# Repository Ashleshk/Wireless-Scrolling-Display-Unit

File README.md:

# Wireless-Scrolling-Display-Unit
 This project was buit for Academic Evaluation of term work for the Third year Mini Project  building in the subject of Electronic Sensor & Mini-Project in Course of E&TC 

## Working Project

## Won Project Exhibition Competition

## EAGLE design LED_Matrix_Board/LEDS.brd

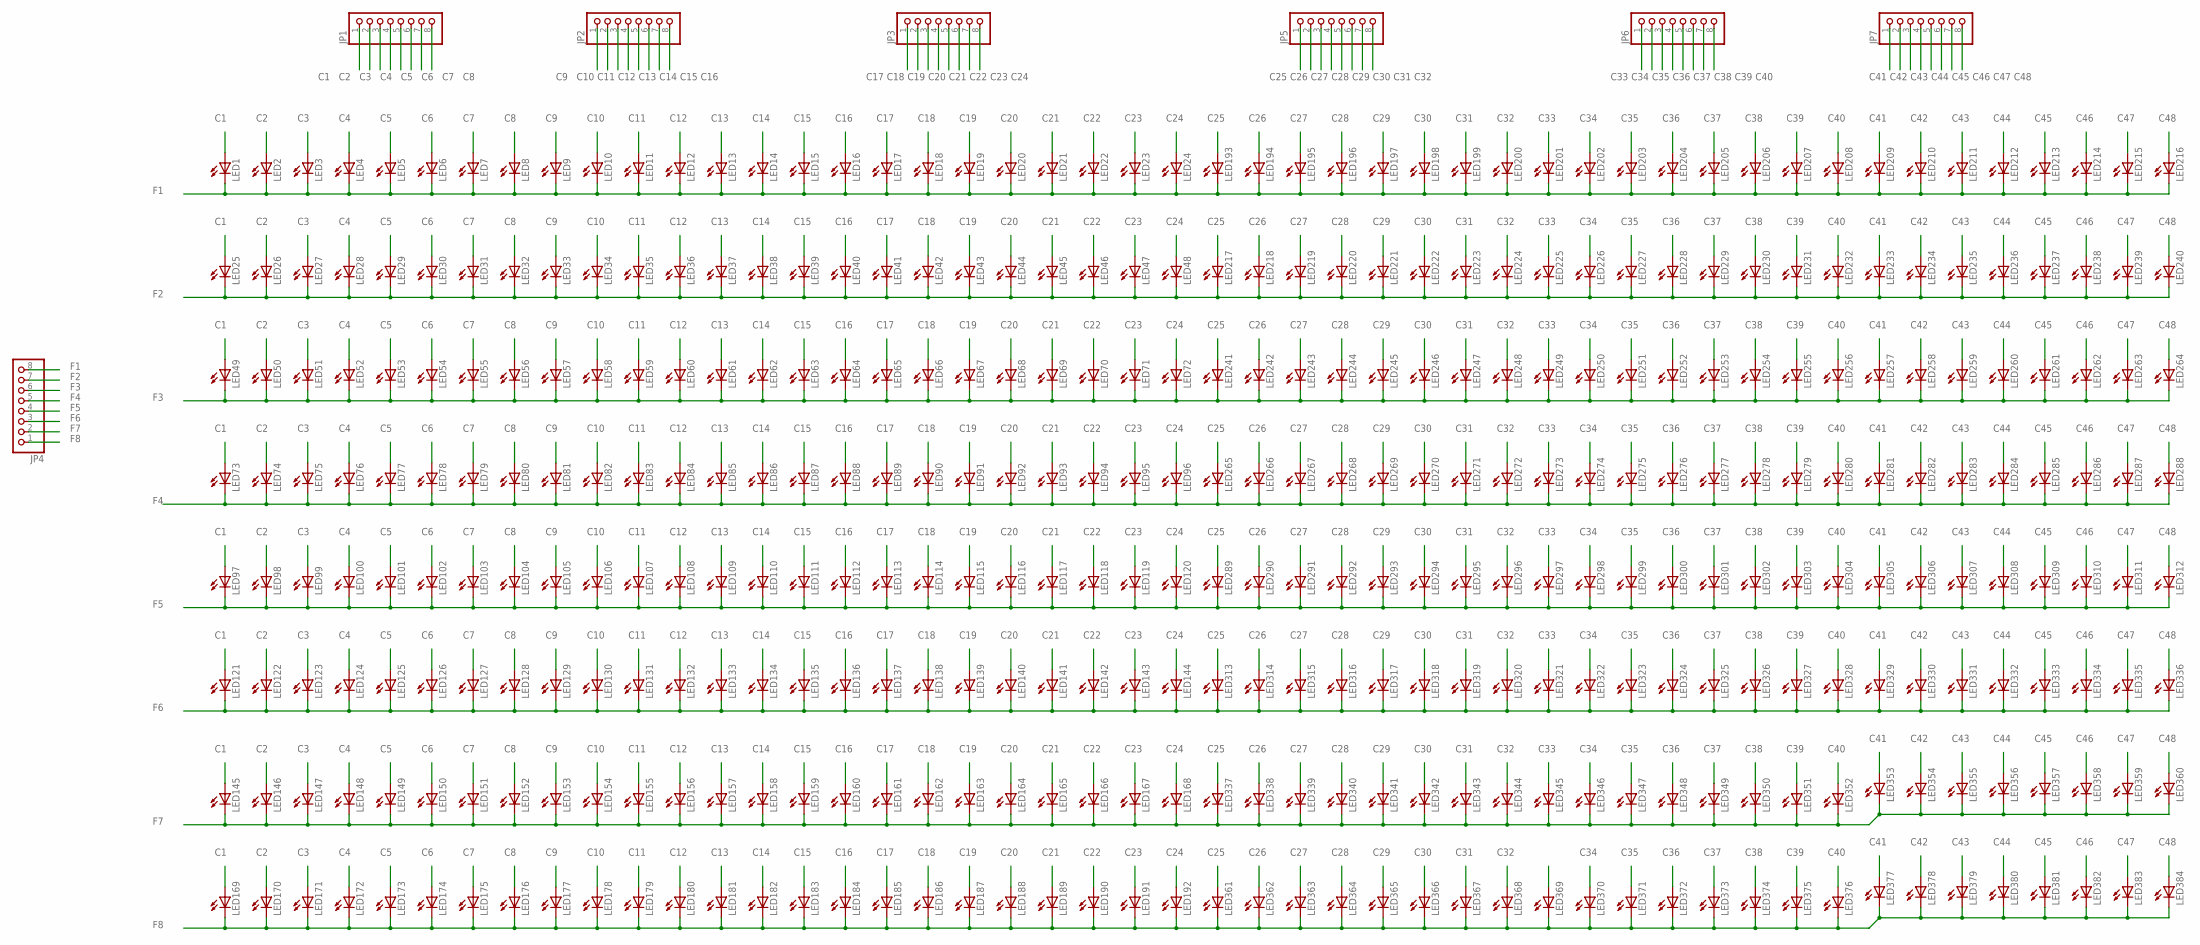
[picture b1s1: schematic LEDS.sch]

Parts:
JP1, JP2, JP3, JP4, JP5, JP6, JP7: PINHD-1X8; 1X08
LED1, LED2, LED3, LED4, LED5, LED6, LED7, LED8, LED9, LED10, LED11, LED12, LED13, LED14, LED15, LED16, LED17, LED18, LED19, LED20, LED21, LED22, LED23, LED24, LED25, LED26, LED27, LED28, LED29, LED30, LED31, LED32, LED33, LED34, LED35, LED36, LED37, LED38, LED39, LED40, LED41, LED42, LED43, LED44, LED45, LED46, LED47, LED48, LED49, LED50, LED51, LED52, LED53, LED54, LED55, LED56, LED57, LED58, LED59, LED60, LED61, LED62, LED63, LED64, LED65, LED66, LED67, LED68, LED69, LED70, LED71, LED72, LED73, LED74, LED75, LED76, LED77, LED78, LED79, LED80, LED81, LED82, LED83, LED84, LED85, LED86, LED87, LED88, LED89, LED90, LED91, LED92, LED93, LED94, LED95, LED96, LED97, LED98, LED99, LED100, LED101, LED102, LED103, LED104, LED105, LED106, LED107, LED108, LED109, LED110, LED111, LED112, LED113, LED114, LED115, LED116, LED117, LED118, LED119, LED120, LED121, LED122, LED123, LED124, LED125, LED126, LED127, LED128, LED129, LED130, LED131, LED132, LED133, LED134, LED135, LED136, LED137, LED138, LED139, LED140, LED141, LED142, LED143, LED144, LED145, LED146, LED147, LED148, LED149, LED150, LED151, LED152, LED153, LED154, LED155, LED156, LED157, LED158, LED159, LED160, LED161, LED162, LED163, LED164, LED165, LED166, LED167, LED168, LED169, LED170, LED171, LED172, LED173, LED174, LED175, LED176, LED177, LED178, LED179, LED180, LED181, LED182, LED183, LED184, LED185, LED186, LED187, LED188, LED189, LED190, LED191, LED192, LED193, LED194, LED195, LED196, LED197, LED198, LED199, LED200, LED201, LED202, LED203, LED204, LED205, LED206, LED207, LED208, LED209, LED210, LED211, LED212, LED213, LED214, LED215, LED216, LED217, LED218, LED219, LED220, LED221, LED222, LED223, LED224, LED225, LED226, LED227, LED228, LED229, LED230, LED231, LED232, LED233, LED234, LED235, LED236, LED237, LED238, LED239, LED240, LED241, LED242, LED243, LED244, LED245, LED246, LED247, LED248, LED249, LED250, LED251, LED252, LED253, LED254, LED255, LED256, LED257, LED258, LED259, LED260, LED261, LED262, LED263, LED264, LED265, LED266, LED267, LED268, LED269, LED270, LED271, LED272, LED273, LED274, LED275, LED276, LED277, LED278, LED279, LED280, LED281, LED282, LED283, LED284, LED285, LED286, LED287, LED288, LED289, LED290, LED291, LED292, LED293, LED294, LED295, LED296, LED297, LED298, LED299, LED300, LED301, LED302, LED303, LED304, LED305, LED306, LED307, LED308, LED309, LED310, LED311, LED312, LED313, LED314, LED315, LED316, LED317, LED318, LED319, LED320, LED321, LED322, LED323, LED324, LED325, LED326, LED327, LED328, LED329, LED330, LED331, LED332, LED333, LED334, LED335, LED336, LED337, LED338, LED339, LED340, LED341, LED342, LED343, LED344, LED345, LED346, LED347, LED348, LED349, LED350, LED351, LED352, LED353, LED354, LED355, LED356, LED357, LED358, LED359, LED360, LED361, LED362, LED363, LED364, LED365, LED366, LED367, LED368, LED369, LED370, LED371, LED372, LED373, LED374, LED375, LED376, LED377, LED378, LED379, LED380, LED381, LED382, LED383, LED384: LED5MM

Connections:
C1: JP1.1, LED1.A, LED25.A, LED49.A, LED73.A, LED97.A, LED121.A, LED145.A, LED169.A
C2: JP1.2, LED2.A, LED26.A, LED50.A, LED74.A, LED98.A, LED122.A, LED146.A, LED170.A
C3: JP1.3, LED3.A, LED27.A, LED51.A, LED75.A, LED99.A, LED123.A, LED147.A, LED171.A
C4: JP1.4, LED4.A, LED28.A, LED52.A, LED76.A, LED100.A, LED124.A, LED148.A, LED172.A
C5: JP1.5, LED5.A, LED29.A, LED53.A, LED77.A, LED101.A, LED125.A, LED149.A, LED173.A
C6: JP1.6, LED6.A, LED30.A, LED54.A, LED78.A, LED102.A, LED126.A, LED150.A, LED174.A
C7: JP1.7, LED7.A, LED31.A, LED55.A, LED79.A, LED103.A, LED127.A, LED151.A, LED175.A
C8: JP1.8, LED8.A, LED32.A, LED56.A, LED80.A, LED104.A, LED128.A, LED152.A, LED176.A
C9: JP2.1, LED9.A, LED33.A, LED57.A, LED81.A, LED105.A, LED129.A, LED153.A, LED177.A
C10: JP2.2, LED10.A, LED34.A, LED58.A, LED82.A, LED106.A, LED130.A, LED154.A, LED178.A
C11: JP2.3, LED11.A, LED35.A, LED59.A, LED83.A, LED107.A, LED131.A, LED155.A, LED179.A
C12: JP2.4, LED12.A, LED36.A, LED60.A, LED84.A, LED108.A, LED132.A, LED156.A, LED180.A
C13: JP2.5, LED13.A, LED37.A, LED61.A, LED85.A, LED109.A, LED133.A, LED157.A, LED181.A
C14: JP2.6, LED14.A, LED38.A, LED62.A, LED86.A, LED110.A, LED134.A, LED158.A, LED182.A
C15: JP2.7, LED15.A, LED39.A, LED63.A, LED87.A, LED111.A, LED135.A, LED159.A, LED183.A
C16: JP2.8, LED16.A, LED40.A, LED64.A, LED88.A, LED112.A, LED136.A, LED160.A, LED184.A
C17: JP3.1, LED17.A, LED41.A, LED65.A, LED89.A, LED113.A, LED137.A, LED161.A, LED185.A
C18: JP3.2, LED18.A, LED42.A, LED66.A, LED90.A, LED114.A, LED138.A, LED162.A, LED186.A
C19: JP3.3, LED19.A, LED43.A, LED67.A, LED91.A, LED115.A, LED139.A, LED163.A, LED187.A
C20: JP3.4, LED20.A, LED44.A, LED68.A, LED92.A, LED116.A, LED140.A, LED164.A, LED188.A
C21: JP3.5, LED21.A, LED45.A, LED69.A, LED93.A, LED117.A, LED141.A, LED165.A, LED189.A
C22: JP3.6, LED22.A, LED46.A, LED70.A, LED94.A, LED118.A, LED142.A, LED166.A, LED190.A
C23: JP3.7, LED23.A, LED47.A, LED71.A, LED95.A, LED119.A, LED143.A, LED167.A, LED191.A
C24: JP3.8, LED24.A, LED48.A, LED72.A, LED96.A, LED120.A, LED144.A, LED168.A, LED192.A
C25: JP5.1, LED193.A, LED217.A, LED241.A, LED265.A, LED289.A, LED313.A, LED337.A, LED361.A
C26: JP5.2, LED194.A, LED218.A, LED242.A, LED266.A, LED290.A, LED314.A, LED338.A, LED362.A
C27: JP5.3, LED195.A, LED219.A, LED243.A, LED267.A, LED291.A, LED315.A, LED339.A, LED363.A
C28: JP5.4, LED196.A, LED220.A, LED244.A, LED268.A, LED292.A, LED316.A, LED340.A, LED364.A
C29: JP5.5, LED197.A, LED221.A, LED245.A, LED269.A, LED293.A, LED317.A, LED341.A, LED365.A
C30: JP5.6, LED198.A, LED222.A, LED246.A, LED270.A, LED294.A, LED318.A, LED342.A, LED366.A
C31: JP5.7, LED199.A, LED223.A, LED247.A, LED271.A, LED295.A, LED319.A, LED343.A, LED367.A
C32: JP5.8, LED200.A, LED224.A, LED248.A, LED272.A, LED296.A, LED320.A, LED344.A, LED368.A
C33: JP6.1, LED201.A, LED225.A, LED249.A, LED273.A, LED297.A, LED321.A, LED345.A
C34: JP6.2, LED202.A, LED226.A, LED250.A, LED274.A, LED298.A, LED322.A, LED346.A, LED370.A
C35: JP6.3, LED203.A, LED227.A, LED251.A, LED275.A, LED299.A, LED323.A, LED347.A, LED371.A
C36: JP6.4, LED204.A, LED228.A, LED252.A, LED276.A, LED300.A, LED324.A, LED348.A, LED372.A
C37: JP6.5, LED205.A, LED229.A, LED253.A, LED277.A, LED301.A, LED325.A, LED349.A, LED373.A
C38: JP6.6, LED206.A, LED230.A, LED254.A, LED278.A, LED302.A, LED326.A, LED350.A, LED374.A
C39: JP6.7, LED207.A, LED231.A, LED255.A, LED279.A, LED303.A, LED327.A, LED351.A, LED375.A
C40: JP6.8, LED208.A, LED232.A, LED256.A, LED280.A, LED304.A, LED328.A, LED352.A, LED376.A
C41: JP7.1, LED209.A, LED233.A, LED257.A, LED281.A, LED305.A, LED329.A, LED353.A, LED369.A, LED377.A
C42: JP7.2, LED210.A, LED234.A, LED258.A, LED282.A, LED306.A, LED330.A, LED354.A, LED378.A
C43: JP7.3, LED211.A, LED235.A, LED259.A, LED283.A, LED307.A, LED331.A, LED355.A, LED379.A
C44: JP7.4, LED212.A, LED236.A, LED260.A, LED284.A, LED308.A, LED332.A, LED356.A, LED380.A
C45: JP7.5, LED213.A, LED237.A, LED261.A, LED285.A, LED309.A, LED333.A, LED357.A, LED381.A
C46: JP7.6, LED214.A, LED238.A, LED262.A, LED286.A, LED310.A, LED334.A, LED358.A, LED382.A
C47: JP7.7, LED215.A, LED239.A, LED263.A, LED287.A, LED311.A, LED335.A, LED359.A, LED383.A
C48: JP7.8, LED216.A, LED240.A, LED264.A, LED288.A, LED312.A, LED336.A, LED360.A, LED384.A
F1: JP4.8, LED1.K (C), LED2.K (C), LED3.K (C), LED4.K (C), LED5.K (C), LED6.K (C), LED7.K (C), LED8.K (C), LED9.K (C), LED10.K (C), LED11.K (C), LED12.K (C), LED13.K (C), LED14.K (C), LED15.K (C), LED16.K (C), LED17.K (C), LED18.K (C), LED19.K (C), LED20.K (C), LED21.K (C), LED22.K (C), LED23.K (C), LED24.K (C), LED193.K (C), LED194.K (C), LED195.K (C), LED196.K (C), LED197.K (C), LED198.K (C), LED199.K (C), LED200.K (C), LED201.K (C), LED202.K (C), LED203.K (C), LED204.K (C), LED205.K (C), LED206.K (C), LED207.K (C), LED208.K (C), LED209.K (C), LED210.K (C), LED211.K (C), LED212.K (C), LED213.K (C), LED214.K (C), LED215.K (C), LED216.K (C)
F2: JP4.7, LED25.K (C), LED26.K (C), LED27.K (C), LED28.K (C), LED29.K (C), LED30.K (C), LED31.K (C), LED32.K (C), LED33.K (C), LED34.K (C), LED35.K (C), LED36.K (C), LED37.K (C), LED38.K (C), LED39.K (C), LED40.K (C), LED41.K (C), LED42.K (C), LED43.K (C), LED44.K (C), LED45.K (C), LED46.K (C), LED47.K (C), LED48.K (C), LED217.K (C), LED218.K (C), LED219.K (C), LED220.K (C), LED221.K (C), LED222.K (C), LED223.K (C), LED224.K (C), LED225.K (C), LED226.K (C), LED227.K (C), LED228.K (C), LED229.K (C), LED230.K (C), LED231.K (C), LED232.K (C), LED233.K (C), LED234.K (C), LED235.K (C), LED236.K (C), LED237.K (C), LED238.K (C), LED239.K (C), LED240.K (C)
F3: JP4.6, LED49.K (C), LED50.K (C), LED51.K (C), LED52.K (C), LED53.K (C), LED54.K (C), LED55.K (C), LED56.K (C), LED57.K (C), LED58.K (C), LED59.K (C), LED60.K (C), LED61.K (C), LED62.K (C), LED63.K (C), LED64.K (C), LED65.K (C), LED66.K (C), LED67.K (C), LED68.K (C), LED69.K (C), LED70.K (C), LED71.K (C), LED72.K (C), LED241.K (C), LED242.K (C), LED243.K (C), LED244.K (C), LED245.K (C), LED246.K (C), LED247.K (C), LED248.K (C), LED249.K (C), LED250.K (C), LED251.K (C), LED252.K (C), LED253.K (C), LED254.K (C), LED255.K (C), LED256.K (C), LED257.K (C), LED258.K (C), LED259.K (C), LED260.K (C), LED261.K (C), LED262.K (C), LED263.K (C), LED264.K (C)
F4: JP4.5, LED73.K (C), LED74.K (C), LED75.K (C), LED76.K (C), LED77.K (C), LED78.K (C), LED79.K (C), LED80.K (C), LED81.K (C), LED82.K (C), LED83.K (C), LED84.K (C), LED85.K (C), LED86.K (C), LED87.K (C), LED88.K (C), LED89.K (C), LED90.K (C), LED91.K (C), LED92.K (C), LED93.K (C), LED94.K (C), LED95.K (C), LED96.K (C), LED265.K (C), LED266.K (C), LED267.K (C), LED268.K (C), LED269.K (C), LED270.K (C), LED271.K (C), LED272.K (C), LED273.K (C), LED274.K (C), LED275.K (C), LED276.K (C), LED277.K (C), LED278.K (C), LED279.K (C), LED280.K (C), LED281.K (C), LED282.K (C), LED283.K (C), LED284.K (C), LED285.K (C), LED286.K (C), LED287.K (C), LED288.K (C)
F5: JP4.4, LED97.K (C), LED98.K (C), LED99.K (C), LED100.K (C), LED101.K (C), LED102.K (C), LED103.K (C), LED104.K (C), LED105.K (C), LED106.K (C), LED107.K (C), LED108.K (C), LED109.K (C), LED110.K (C), LED111.K (C), LED112.K (C), LED113.K (C), LED114.K (C), LED115.K (C), LED116.K (C), LED117.K (C), LED118.K (C), LED119.K (C), LED120.K (C), LED289.K (C), LED290.K (C), LED291.K (C), LED292.K (C), LED293.K (C), LED294.K (C), LED295.K (C), LED296.K (C), LED297.K (C), LED298.K (C), LED299.K (C), LED300.K (C), LED301.K (C), LED302.K (C), LED303.K (C), LED304.K (C), LED305.K (C), LED306.K (C), LED307.K (C), LED308.K (C), LED309.K (C), LED310.K (C), LED311.K (C), LED312.K (C)
F6: JP4.3, LED121.K (C), LED122.K (C), LED123.K (C), LED124.K (C), LED125.K (C), LED126.K (C), LED127.K (C), LED128.K (C), LED129.K (C), LED130.K (C), LED131.K (C), LED132.K (C), LED133.K (C), LED134.K (C), LED135.K (C), LED136.K (C), LED137.K (C), LED138.K (C), LED139.K (C), LED140.K (C), LED141.K (C), LED142.K (C), LED143.K (C), LED144.K (C), LED313.K (C), LED314.K (C), LED315.K (C), LED316.K (C), LED317.K (C), LED318.K (C), LED319.K (C), LED320.K (C), LED321.K (C), LED322.K (C), LED323.K (C), LED324.K (C), LED325.K (C), LED326.K (C), LED327.K (C), LED328.K (C), LED329.K (C), LED330.K (C), LED331.K (C), LED332.K (C), LED333.K (C), LED334.K (C), LED335.K (C), LED336.K (C)
F7: JP4.2, LED145.K (C), LED146.K (C), LED147.K (C), LED148.K (C), LED149.K (C), LED150.K (C), LED151.K (C), LED152.K (C), LED153.K (C), LED154.K (C), LED155.K (C), LED156.K (C), LED157.K (C), LED158.K (C), LED159.K (C), LED160.K (C), LED161.K (C), LED162.K (C), LED163.K (C), LED164.K (C), LED165.K (C), LED166.K (C), LED167.K (C), LED168.K (C), LED337.K (C), LED338.K (C), LED339.K (C), LED340.K (C), LED341.K (C), LED342.K (C), LED343.K (C), LED344.K (C), LED345.K (C), LED346.K (C), LED347.K (C), LED348.K (C), LED349.K (C), LED350.K (C), LED351.K (C), LED352.K (C), LED353.K (C), LED354.K (C), LED355.K (C), LED356.K (C), LED357.K (C), LED358.K (C), LED359.K (C), LED360.K (C)
F8: JP4.1, LED169.K (C), LED170.K (C), LED171.K (C), LED172.K (C), LED173.K (C), LED174.K (C), LED175.K (C), LED176.K (C), LED177.K (C), LED178.K (C), LED179.K (C), LED180.K (C), LED181.K (C), LED182.K (C), LED183.K (C), LED184.K (C), LED185.K (C), LED186.K (C), LED187.K (C), LED188.K (C), LED189.K (C), LED190.K (C), LED191.K (C), LED192.K (C), LED361.K (C), LED362.K (C), LED363.K (C), LED364.K (C), LED365.K (C), LED366.K (C), LED367.K (C), LED368.K (C), LED369.K (C), LED370.K (C), LED371.K (C), LED372.K (C), LED373.K (C), LED374.K (C), LED375.K (C), LED376.K (C), LED377.K (C), LED378.K (C), LED379.K (C), LED380.K (C), LED381.K (C), LED382.K (C), LED383.K (C), LED384.K (C)

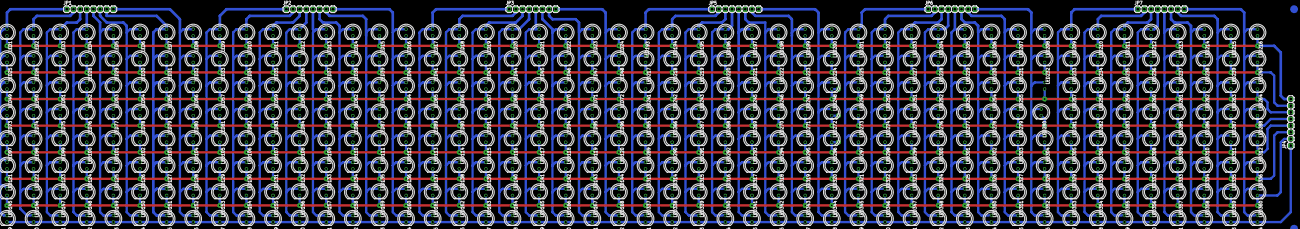
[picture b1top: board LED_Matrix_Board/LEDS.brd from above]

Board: 2 copper layers, 391 parts (1 on the bottom side), 56 nets.

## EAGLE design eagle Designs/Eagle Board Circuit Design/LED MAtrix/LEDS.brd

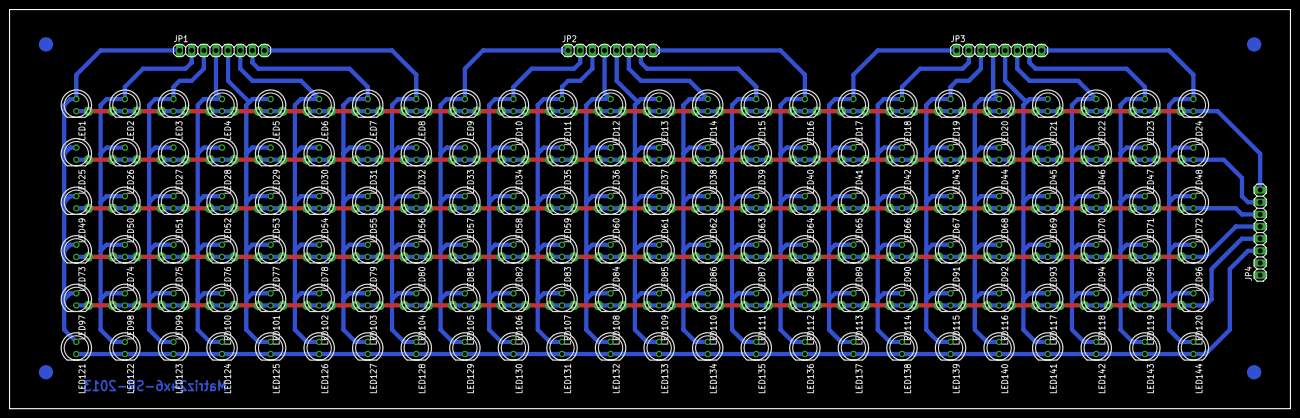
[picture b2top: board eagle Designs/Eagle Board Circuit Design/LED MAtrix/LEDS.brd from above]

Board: 2 copper layers, 267.9 x 83.5 mm, 148 parts (0 on the bottom side), 30 nets.

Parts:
JP1, JP2, JP3, JP4: 1X08
LED1, LED2, LED3, LED4, LED5, LED6, LED7, LED8, LED9, LED10, LED11, LED12, LED13, LED14, LED15, LED16, LED17, LED18, LED19, LED20, LED21, LED22, LED23, LED24, LED25, LED26, LED27, LED28, LED29, LED30, LED31, LED32, LED33, LED34, LED35, LED36, LED37, LED38, LED39, LED40, LED41, LED42, LED43, LED44, LED45, LED46, LED47, LED48, LED49, LED50, LED51, LED52, LED53, LED54, LED55, LED56, LED57, LED58, LED59, LED60, LED61, LED62, LED63, LED64, LED65, LED66, LED67, LED68, LED69, LED70, LED71, LED72, LED73, LED74, LED75, LED76, LED77, LED78, LED79, LED80, LED81, LED82, LED83, LED84, LED85, LED86, LED87, LED88, LED89, LED90, LED91, LED92, LED93, LED94, LED95, LED96, LED97, LED98, LED99, LED100, LED101, LED102, LED103, LED104, LED105, LED106, LED107, LED108, LED109, LED110, LED111, LED112, LED113, LED114, LED115, LED116, LED117, LED118, LED119, LED120, LED121, LED122, LED123, LED124, LED125, LED126, LED127, LED128, LED129, LED130, LED131, LED132, LED133, LED134, LED135, LED136, LED137, LED138, LED139, LED140, LED141, LED142, LED143, LED144: LED5MM

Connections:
C1: JP1.1, LED1.A, LED25.A, LED49.A, LED73.A, LED97.A, LED121.A
C2: JP1.2, LED2.A, LED26.A, LED50.A, LED74.A, LED98.A, LED122.A
C3: JP1.3, LED3.A, LED27.A, LED51.A, LED75.A, LED99.A, LED123.A
C4: JP1.4, LED4.A, LED28.A, LED52.A, LED76.A, LED100.A, LED124.A
C5: JP1.5, LED5.A, LED29.A, LED53.A, LED77.A, LED101.A, LED125.A
C6: JP1.6, LED6.A, LED30.A, LED54.A, LED78.A, LED102.A, LED126.A
C7: JP1.7, LED7.A, LED31.A, LED55.A, LED79.A, LED103.A, LED127.A
C8: JP1.8, LED8.A, LED32.A, LED56.A, LED80.A, LED104.A, LED128.A
C9: JP2.1, LED9.A, LED33.A, LED57.A, LED81.A, LED105.A, LED129.A
C10: JP2.2, LED10.A, LED34.A, LED58.A, LED82.A, LED106.A, LED130.A
C11: JP2.3, LED11.A, LED35.A, LED59.A, LED83.A, LED107.A, LED131.A
C12: JP2.4, LED12.A, LED36.A, LED60.A, LED84.A, LED108.A, LED132.A
C13: JP2.5, LED13.A, LED37.A, LED61.A, LED85.A, LED109.A, LED133.A
C14: JP2.6, LED14.A, LED38.A, LED62.A, LED86.A, LED110.A, LED134.A
C15: JP2.7, LED15.A, LED39.A, LED63.A, LED87.A, LED111.A, LED135.A
C16: JP2.8, LED16.A, LED40.A, LED64.A, LED88.A, LED112.A, LED136.A
C17: JP3.1, LED17.A, LED41.A, LED65.A, LED89.A, LED113.A, LED137.A
C18: JP3.2, LED18.A, LED42.A, LED66.A, LED90.A, LED114.A, LED138.A
C19: JP3.3, LED19.A, LED43.A, LED67.A, LED91.A, LED115.A, LED139.A
C20: JP3.4, LED20.A, LED44.A, LED68.A, LED92.A, LED116.A, LED140.A
C21: JP3.5, LED21.A, LED45.A, LED69.A, LED93.A, LED117.A, LED141.A
C22: JP3.6, LED22.A, LED46.A, LED70.A, LED94.A, LED118.A, LED142.A
C23: JP3.7, LED23.A, LED47.A, LED71.A, LED95.A, LED119.A, LED143.A
C24: JP3.8, LED24.A, LED48.A, LED72.A, LED96.A, LED120.A, LED144.A
F1: JP4.8, LED1.K, LED2.K, LED3.K, LED4.K, LED5.K, LED6.K, LED7.K, LED8.K, LED9.K, LED10.K, LED11.K, LED12.K, LED13.K, LED14.K, LED15.K, LED16.K, LED17.K, LED18.K, LED19.K, LED20.K, LED21.K, LED22.K, LED23.K, LED24.K
F2: JP4.7, LED25.K, LED26.K, LED27.K, LED28.K, LED29.K, LED30.K, LED31.K, LED32.K, LED33.K, LED34.K, LED35.K, LED36.K, LED37.K, LED38.K, LED39.K, LED40.K, LED41.K, LED42.K, LED43.K, LED44.K, LED45.K, LED46.K, LED47.K, LED48.K
F3: JP4.6, LED49.K, LED50.K, LED51.K, LED52.K, LED53.K, LED54.K, LED55.K, LED56.K, LED57.K, LED58.K, LED59.K, LED60.K, LED61.K, LED62.K, LED63.K, LED64.K, LED65.K, LED66.K, LED67.K, LED68.K, LED69.K, LED70.K, LED71.K, LED72.K
F4: JP4.5, LED73.K, LED74.K, LED75.K, LED76.K, LED77.K, LED78.K, LED79.K, LED80.K, LED81.K, LED82.K, LED83.K, LED84.K, LED85.K, LED86.K, LED87.K, LED88.K, LED89.K, LED90.K, LED91.K, LED92.K, LED93.K, LED94.K, LED95.K, LED96.K
F5: JP4.4, LED97.K, LED98.K, LED99.K, LED100.K, LED101.K, LED102.K, LED103.K, LED104.K, LED105.K, LED106.K, LED107.K, LED108.K, LED109.K, LED110.K, LED111.K, LED112.K, LED113.K, LED114.K, LED115.K, LED116.K, LED117.K, LED118.K, LED119.K, LED120.K
F6: JP4.3, LED121.K, LED122.K, LED123.K, LED124.K, LED125.K, LED126.K, LED127.K, LED128.K, LED129.K, LED130.K, LED131.K, LED132.K, LED133.K, LED134.K, LED135.K, LED136.K, LED137.K, LED138.K, LED139.K, LED140.K, LED141.K, LED142.K, LED143.K, LED144.K

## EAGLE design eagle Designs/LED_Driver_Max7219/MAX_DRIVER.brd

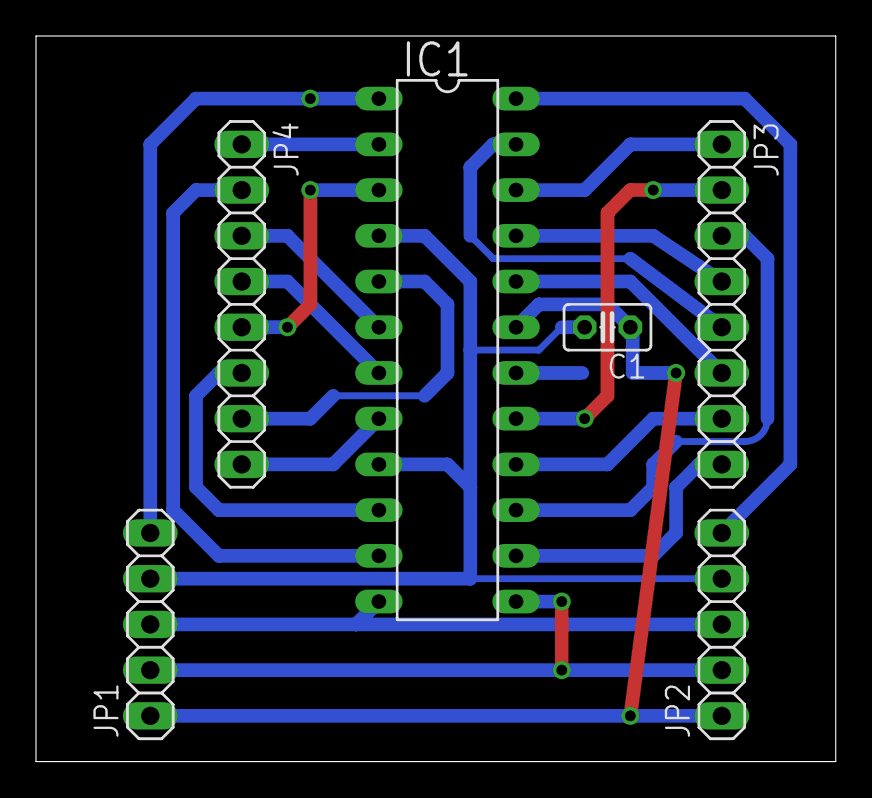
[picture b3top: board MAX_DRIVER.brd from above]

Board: 2 copper layers, 44.4 x 40.3 mm, 7 parts (1 on the bottom side), 23 nets.

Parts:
C1: C025-025X050
IC1: MAX7219CNG; DIL24-3
JP1, JP2: 1X05
JP3, JP4: 1X08
R1: M1206

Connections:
C1: IC1.14, JP3.8
C2: IC1.16, JP3.7
C3: IC1.20, JP3.6
C4: IC1.23, JP3.5
C5: IC1.21, JP3.4
C6: IC1.15, JP3.3
C7: IC1.17, JP3.2
C8: IC1.22, JP3.1
CLK: IC1.13, JP1.2, JP2.2
CS: IC1.12, JP1.3, JP2.3
DIN: IC1.1, JP1.5
DOUT: IC1.24, JP2.5
GND: C1.2, IC1.4, IC1.9, JP1.4, JP2.4
unnamed: IC1.18, R1.2
R1: IC1.2, JP4.1
R2: IC1.11, JP4.2
R3: IC1.6, JP4.3
R4: IC1.7, JP4.4
R5: IC1.3, JP4.5
R6: IC1.10, JP4.6
R7: IC1.5, JP4.7
R8: IC1.8, JP4.8
VCC: C1.1, IC1.19, JP1.1, JP2.1, R1.1

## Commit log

2020-05-08 Circuit Design & MATRIX board
2020-05-08 Final Code & report
2022-12-16 Upload
2022-12-16 updating Readme
2022-12-26 cropped Proof image
2022-12-26 uplaod image
2022-12-26 updated readme with corrected Image
2022-12-26 uplaod
